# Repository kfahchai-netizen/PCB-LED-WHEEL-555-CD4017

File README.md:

<div align="center">

# 🎡 LED Wheel: NE555 + CD4017 Running-Light PCB

**A round, 80 mm, 2-layer through-hole PCB in KiCad: a 555 timer clocks a CD4017 decade counter that chases a ring of 10 LEDs, with a knob to set the speed.**

</div>

---

## 📌 Overview

| | |
|---|---|
| **What it does** | One LED at a time lights up and the light runs round the ring. A green LED blinks with every clock pulse. |
| **Circuit** | NE555 astable oscillator (clock) → CD4017 decade counter (Q0…Q9) → 10 LEDs |
| **Speed** | Trimmer RV1 sets about **1.4 Hz to 14.6 Hz** (steps per second) |
| **Power** | 5–12 V DC (a 9 V battery is ideal) through a screw terminal, with reverse-polarity protection |
| **Board** | Ø 80 mm round, 2 layers, all through-hole, GND pour on both sides, 4 × M3 mounting holes |
| **Status** | Rev 1.0: design complete, opened and checked in **KiCad 10**: ERC 0 errors, DRC 0 errors, 0 unconnected, PCB ↔ schematic in parity. Gerbers ready. *Not yet fabricated.* |

## 🖼️ Board

<p align="center">
  
  <br><sub>3D view in KiCad 10 (exported from the 3D viewer)</sub>
</p>

<p align="center">
  
  <br><sub>Front (left) and back (right). Renders are made from the actual copper, solder-mask and silkscreen layers.</sub>
</p>

## 🧠 How it works

```mermaid
flowchart LR
    PWR["5–12 V in<br/>J1 + D11 (1N5817)"] --> VCC(("VCC"))
    VCC --> CLK["NE555 astable<br/>R1, R2 + RV1, C1"]
    CLK -- "square wave<br/>1.4–14.6 Hz" --> CNT["CD4017<br/>decade counter"]
    CLK --> D12["Green CLK LED"]
    CNT -- "Q0…Q9<br/>one high at a time" --> LEDS["10 red LEDs<br/>in a ring"]
    LEDS --> R3["Shared 470 Ω<br/>to GND"]
```

### 1. Clock: NE555 astable

C1 charges through R1 + R2 + RV1 and discharges through R2 + RV1 into pin 7. That makes a square wave at

$$f = \frac{1.44}{(R_1 + 2(R_2 + R_{V1}))\,C_1}$$

| RV1 | Frequency | Feel |
|---|---|---|
| 0 Ω | 1.44 / ((1 k + 2·10 k) · 4.7 µF) ≈ **14.6 Hz** | fast spin |
| 50 kΩ | ≈ 2.5 Hz | relaxed |
| 100 kΩ | 1.44 / (221 k · 4.7 µF) ≈ **1.4 Hz** | slow step |

R2 (10 kΩ) sets a minimum resistance, so turning RV1 to zero can't short pin 7 to the timing capacitor. C2 (10 nF) on CV filters noise on the 555's internal comparator reference.

### 2. Counter: CD4017 decade counter

Each rising clock edge moves the single high output along: Q0 → Q1 → … → Q9 → Q0. `RESET` and `CLOCK ENABLE` are tied low, so it counts freely. Carry-out (pin 12) is unused and marked *no-connect* in the schematic.

### 3. LED ring

Each output drives one LED's **anode**. All **cathodes** share **one 470 Ω resistor** to GND. Only one output is ever high, so one resistor is enough: I ≤ (9 V − 2 V) / 470 Ω ≈ 15 mA. In practice the CD4017's output drive limits it to about 5–10 mA. On the PCB the cathode net is a ring track around the outside, and the 10 output tracks fan in from the counter.

### 4. Power and protection

- **D11 (1N5817 Schottky)** in series blocks reverse polarity and drops only about 0.3 V.
- **C3 (100 µF)** is the bulk reservoir; **C4 / C5 (100 nF)** decouple each IC, placed next to its supply pin.

## 📐 Schematic

Full-resolution PDF: [`docs/led_chaser_schematic.pdf`](docs/led_chaser_schematic.pdf)

## 🛠️ PCB design decisions

| Decision | Why |
|---|---|
| **Round 80 mm board, LEDs on a 32 mm radius** | Looks like a wheel; 36° spacing makes the chase smooth |
| **LEDs placed radially, anode inside and cathode outside** | Output tracks come in from the centre and the cathode ring runs round the outside, so no crossings |
| **Net classes:** signals 0.4 mm, power (VIN/VCC/GND) 0.7 mm, 0.3 mm clearance | Easy to fabricate and solder, and comfortably above typical fab limits |
| **GND pour on both layers + thermal reliefs** | Low-impedance return, less copper to etch, pads stay easy to solder |
| **All through-hole parts** | Hand-solderable for a first build or workshop kit |
| **Polarity marks (+/−), "SPEED" and name on the silkscreen** | Fewer assembly mistakes; looks finished |

**Verification**

- The schematic netlist exported by `kicad-cli` is compared with the design description: **all 20 nets match**.
- Every PCB footprint is linked to its schematic symbol (29/29), so *Update PCB from Schematic* works.
- KiCad DRC shows **0 clearance errors and 0 unconnected pads**.
- Opened in **KiCad 10**: ERC 0 errors, DRC 0 errors. The only warnings are KiCad 7 vs KiCad 10 library versions. KiCad 10's checks also caught two issues that were fixed: a screw-terminal footprint removed from the KiCad 10 library, and net names that didn't match KiCad's `/LABEL` naming.

## ⚙️ Design as code

The whole design is generated from one Python description (`tools/design.py`): parts, footprints and every connection. That means the schematic and PCB can never drift apart.

| Script | What it does |
|---|---|
| `tools/gen_sch.py` | Writes the KiCad schematic: places library symbols, net labels, power flags, block frames and notes |
| `tools/gen_pcb.py` | Places footprints (LED ring maths), assigns nets, draws the round outline and silkscreen |
| `tools/astar_router.py` | **A small custom 2-layer autorouter written for this board:** A* search on a 0.2 mm grid, 45° moves, via and bend penalties, obstacles inflated by clearance + half track width, rip-up and retry |
| `tools/route_pcb.py` | Runs the router, adds the GND pours, fills zones and runs KiCad's DRC |
| `tools/render_board.py` | Builds the photo-style renders and the chase animation from the real layer exports |
| `build.sh` | Rebuilds everything: schematic → PCB → routing → Gerbers → docs |

```bash
pip install shapely numpy pillow cairosvg
./build.sh
```

## 🏭 Get it made

1. Upload [`fabrication/led_chaser_gerbers_jlcpcb.zip`](fabrication/led_chaser_gerbers_jlcpcb.zip) to any PCB fab (JLCPCB, PCBWay and others). The defaults are fine: 2 layers, 1.6 mm, HASL or ENIG.
2. Buy the parts in [`fabrication/bom.csv`](fabrication/bom.csv). They're all common through-hole parts.
3. Solder from lowest to tallest: resistors → diode → IC sockets → ceramic caps → LEDs → trimmer → electrolytics → terminal.
4. Watch polarity on **D1–D12** (flat side / square pad = cathode), **C1/C3** (+ marked), **D11** (band = K) and the IC notches.

### Bill of materials

| Qty | Ref | Value | Part |
|---|---|---|---|
| 1 | U1 | NE555P | 555 timer, DIP-8 |
| 1 | U2 | CD4017B | Decade counter, DIP-16 |
| 10 | D1–D10 | Red | 5 mm LED |
| 1 | D12 | Green | 3 mm LED (clock indicator) |
| 1 | D11 | 1N5817 | Schottky diode, DO-41 |
| 2 | R1, R4 | 1 kΩ | ¼ W axial |
| 1 | R2 | 10 kΩ | ¼ W axial |
| 1 | R3 | 470 Ω | ¼ W axial |
| 1 | RV1 | 100 kΩ | Bourns 3386P trimmer |
| 1 | C1 | 4.7 µF | Electrolytic, 5 mm |
| 1 | C3 | 100 µF | Electrolytic, 6.3 mm |
| 1 | C2 | 10 nF | Ceramic disc |
| 2 | C4, C5 | 100 nF | Ceramic disc |
| 1 | J1 | 2-pin | 5.08 mm screw terminal |

## 📁 Project structure

```
├── kicad/                  # KiCad project: .kicad_pro, .kicad_sch, .kicad_pcb (opens in KiCad 7–10)
├── fabrication/
│   ├── gerbers/            # Gerber + Excellon drill files
│   ├── led_chaser_gerbers_jlcpcb.zip
│   └── bom.csv
├── docs/                   # Schematic PDF/SVG, PCB PDF, images
├── tools/                  # Design-as-code generators, A* router, renderer
└── build.sh                # One-command rebuild
```

## 🚀 Ideas for Rev 2

- Replace the 555 with a microcontroller, or an **FPGA / CPLD**, to add patterns such as bounce, fill and random.
- Use **WS2812** addressable LEDs and a USB-C power input.
- Cascade two CD4017s with the carry-out pin for a 20-LED ring.
- Switch to SMD parts and get it assembled at the fab.

## 🔑 Key concepts

`555 astable timing` · `CMOS decade counter` · `schematic capture` · `PCB layout` · `net classes and design rules` · `ground pours and thermal reliefs` · `DRC / ERC` · `Gerber / Excellon fabrication output` · `A* path-finding` · `design automation with the KiCad Python API`

---

<div align="center">
<sub>Made by <b>Kean Fah Chai</b> · Swinburne University of Technology Sarawak</sub>
</div>

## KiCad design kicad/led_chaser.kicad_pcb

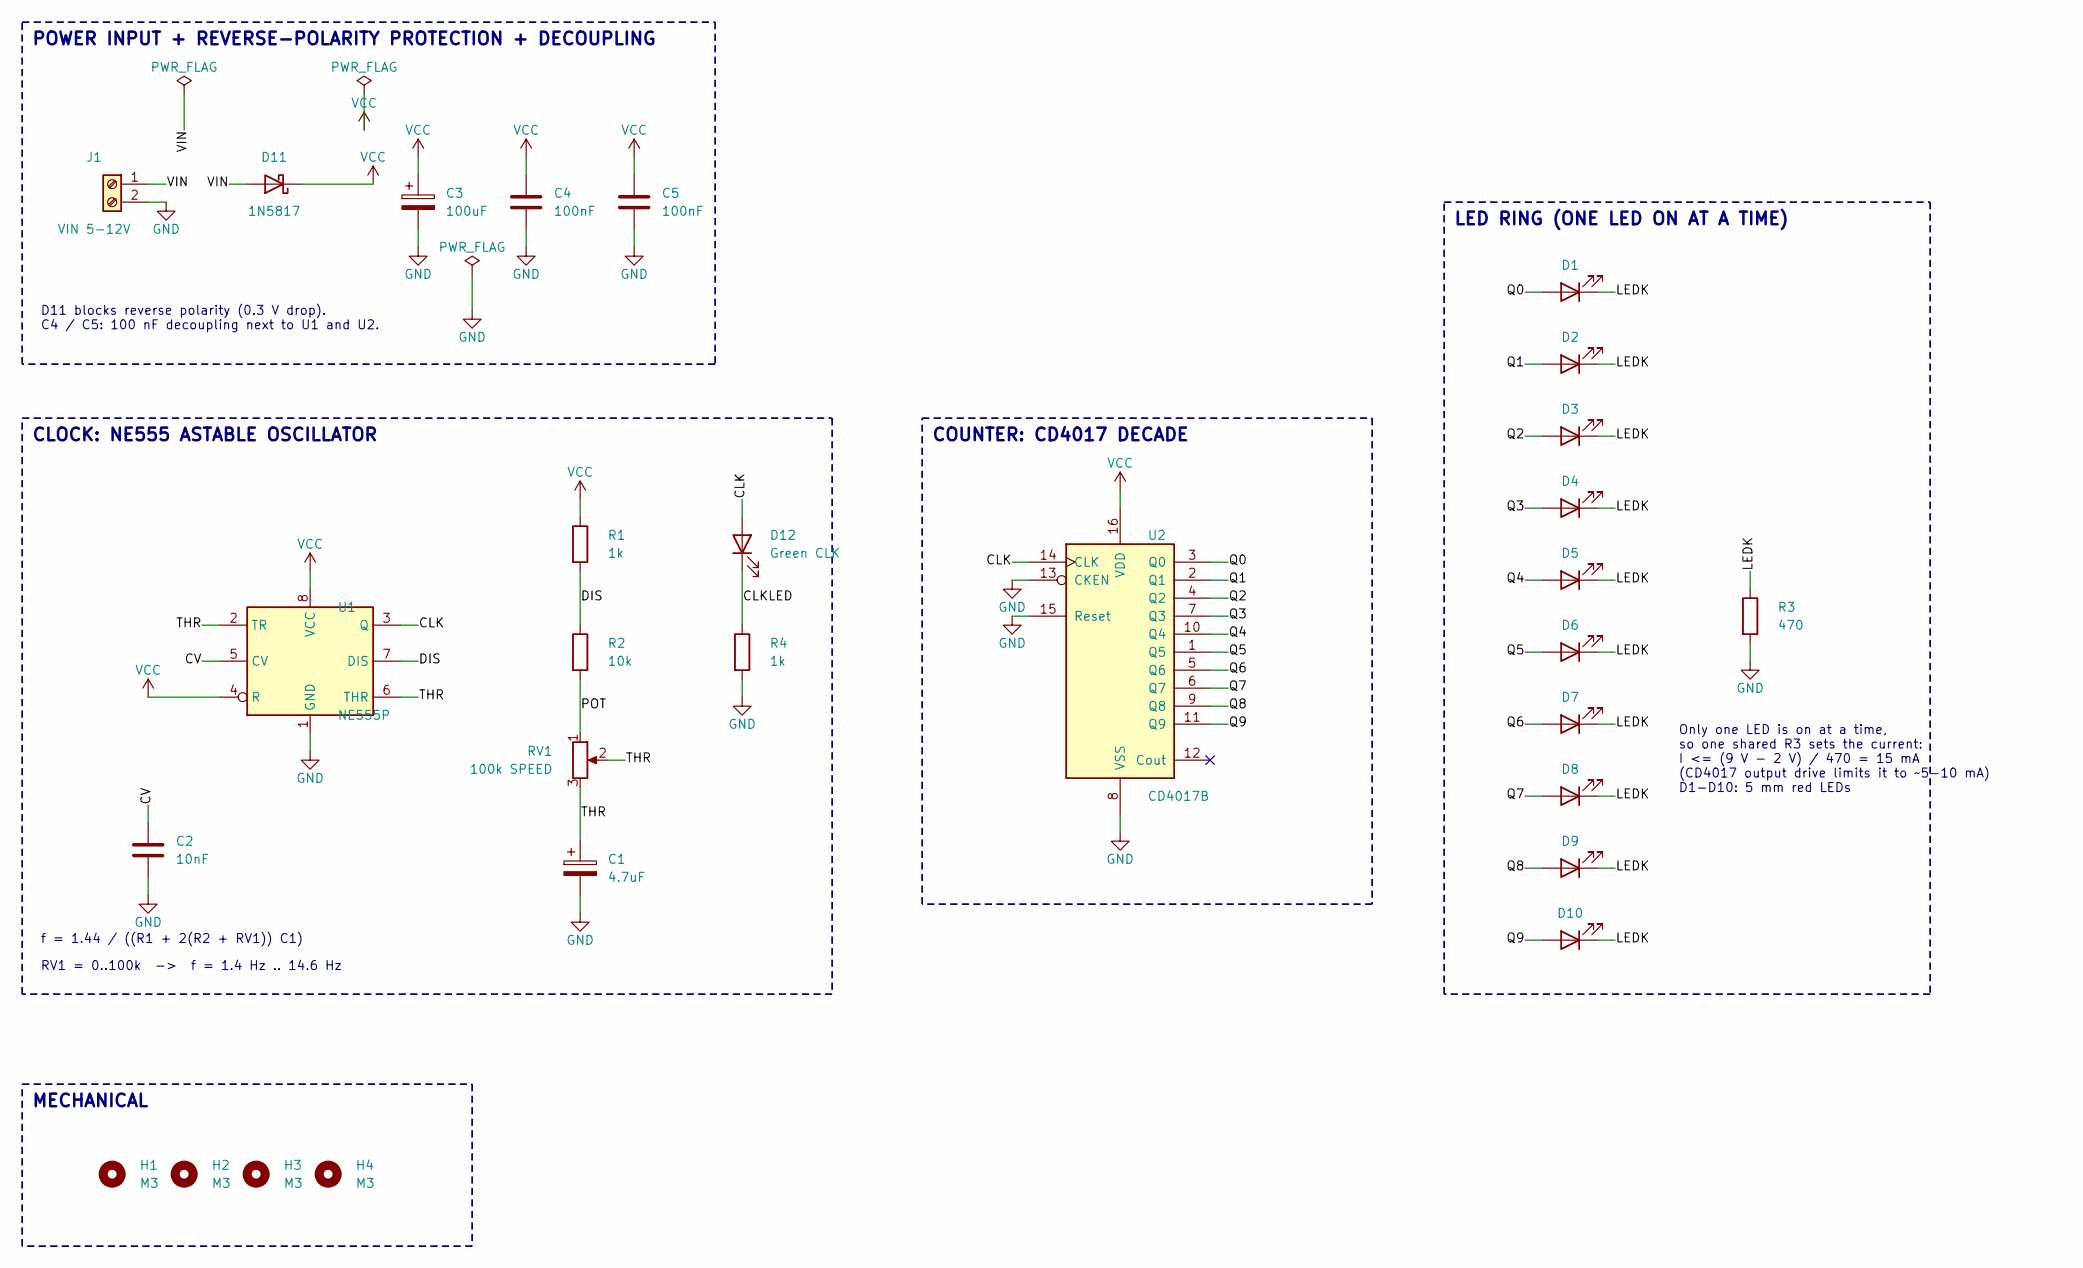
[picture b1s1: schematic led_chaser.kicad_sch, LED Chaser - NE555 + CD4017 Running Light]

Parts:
C1: 4.7uF; CP_Radial_D5.0mm_P2.00mm
C2: 10nF; C_Disc_D5.0mm_W2.5mm_P5.00mm
C3: 100uF; CP_Radial_D6.3mm_P2.50mm
C4, C5: 100nF; C_Disc_D5.0mm_W2.5mm_P5.00mm
D1, D2, D3, D4, D5, D6, D7, D8, D9, D10: Red; LED_D5.0mm
D11: 1N5817; D_DO-41_SOD81_P10.16mm_Horizontal
D12: Green CLK; LED_D3.0mm
H1, H2, H3, H4: M3; MountingHole_3.2mm_M3
J1: VIN 5-12V; TerminalBlock_Phoenix_MKDS-1,5-2-5.08_1x02_P5.08mm_Horizont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
R1, R4: 1k; R_Axial_DIN0207_L6.3mm_D2.5mm_P7.62mm_Horizontal
R2: 10k; R_Axial_DIN0207_L6.3mm_D2.5mm_P7.62mm_Horizontal
R3: 470; R_Axial_DIN0207_L6.3mm_D2.5mm_P7.62mm_Horizontal
RV1: 100k SPEED; Potentiometer_Bourns_3386P_Vertical
U1: NE555P; DIP-8_W7.62mm
U2: CD4017B; DIP-16_W7.62mm

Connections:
/CLK: D12.2 (A), U1.3 (Q), U2.14 (CLK)
/CLKLED: D12.1 (K), R4.1
/CV: C2.1, U1.5 (CV)
/DIS: R1.2, R2.1, U1.7 (DIS)
/LEDK: D1.1 (K), D2.1 (K), D3.1 (K), D4.1 (K), D5.1 (K), D6.1 (K), D7.1 (K), D8.1 (K), D9.1 (K), D10.1 (K), R3.1
/POT: R2.2, RV1.1
/Q0: D1.2 (A), U2.3 (Q0)
/Q1: D2.2 (A), U2.2 (Q1)
/Q2: D3.2 (A), U2.4 (Q2)
/Q3: D4.2 (A), U2.7 (Q3)
/Q4: D5.2 (A), U2.10 (Q4)
/Q5: D6.2 (A), U2.1 (Q5)
/Q6: D7.2 (A), U2.5 (Q6)
/Q7: D8.2 (A), U2.6 (Q7)
/Q8: D9.2 (A), U2.9 (Q8)
/Q9: D10.2 (A), U2.11 (Q9)
/THR: C1.1, RV1.2, RV1.3, U1.2 (TR), U1.6 (THR)
/VIN: D11.2 (A), J1.1
GND: C1.2, C2.2, C3.2, C4.2, C5.2, J1.2, R3.2, R4.2, U1.1 (GND), U2.8 (VSS), U2.13 (CKEN), U2.15 (Reset)
VCC: C3.1, C4.1, C5.1, D11.1 (K), R1.1, U1.4 (R), U1.8 (VCC), U2.16 (VDD)

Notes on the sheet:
POWER INPUT + REVERSE-POLARITY PROTECTION + DECOUPLING
CLOCK: NE555 ASTABLE OSCILLATOR
COUNTER: CD4017 DECADE
LED RING (ONE LED ON AT A TIME)
f = 1.44 / ((R1 + 2(R2 + RV1)) C1)
RV1 = 0..100k -> f = 1.4 Hz .. 14.6 Hz
Only one LED is on at a time, so one shared R3 sets the current: I <= (9 V - 2 V) / 470 = 15 mA (CD4017 output drive limits it to ~5-10 mA) D1-D10: 5 mm red LEDs
D11 blocks reverse polarity (0.3 V drop). C4 / C5: 100 nF decoupling next to U1 and U2.
MECHANICAL

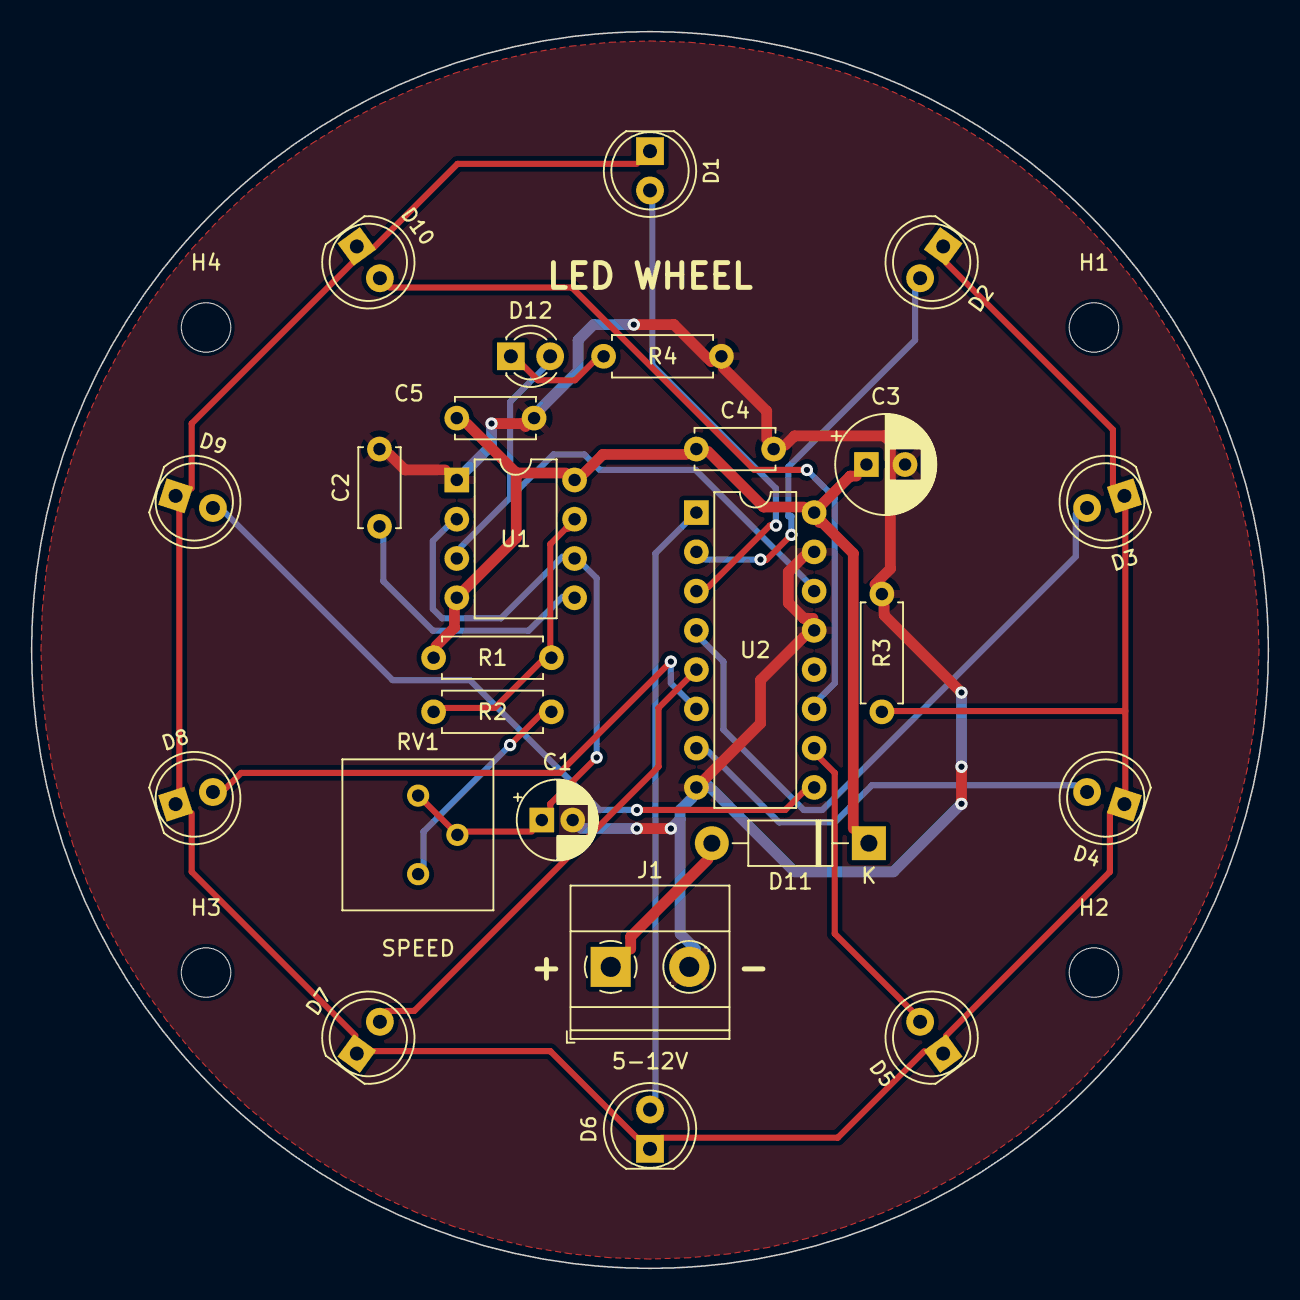
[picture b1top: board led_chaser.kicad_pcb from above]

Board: 2 copper layers, 80.0 x 80.0 mm, 29 parts (0 on the bottom side), 20 nets.

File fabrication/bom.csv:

Qty,References,Value,Footprint
1,C1,4.7uF,CP_Radial_D5.0mm_P2.00mm
1,C2,10nF,C_Disc_D5.0mm_W2.5mm_P5.00mm
1,C3,100uF,CP_Radial_D6.3mm_P2.50mm
2,C4 C5,100nF,C_Disc_D5.0mm_W2.5mm_P5.00mm
10,D1 D2 D3 D4 D5 D6 D7 D8 D9 D10,Red,LED_D5.0mm
1,D11,1N5817,D_DO-41_SOD81_P10.16mm_Horizontal
1,D12,Green CLK,LED_D3.0mm
1,J1,VIN 5-12V,"TerminalBlock_Phoenix_MKDS-1,5-2-5.08_1x02_P5.08mm_Horizontal"
2,R1 R4,1k,R_Axial_DIN0207_L6.3mm_D2.5mm_P7.62mm_Horizontal
1,R2,10k,R_Axial_DIN0207_L6.3mm_D2.5mm_P7.62mm_Horizontal
1,R3,470,R_Axial_DIN0207_L6.3mm_D2.5mm_P7.62mm_Horizontal
1,RV1,100k SPEED,Potentiometer_Bourns_3386P_Vertical
1,U1,NE555P,DIP-8_W7.62mm
1,U2,CD4017B,DIP-16_W7.62mm
